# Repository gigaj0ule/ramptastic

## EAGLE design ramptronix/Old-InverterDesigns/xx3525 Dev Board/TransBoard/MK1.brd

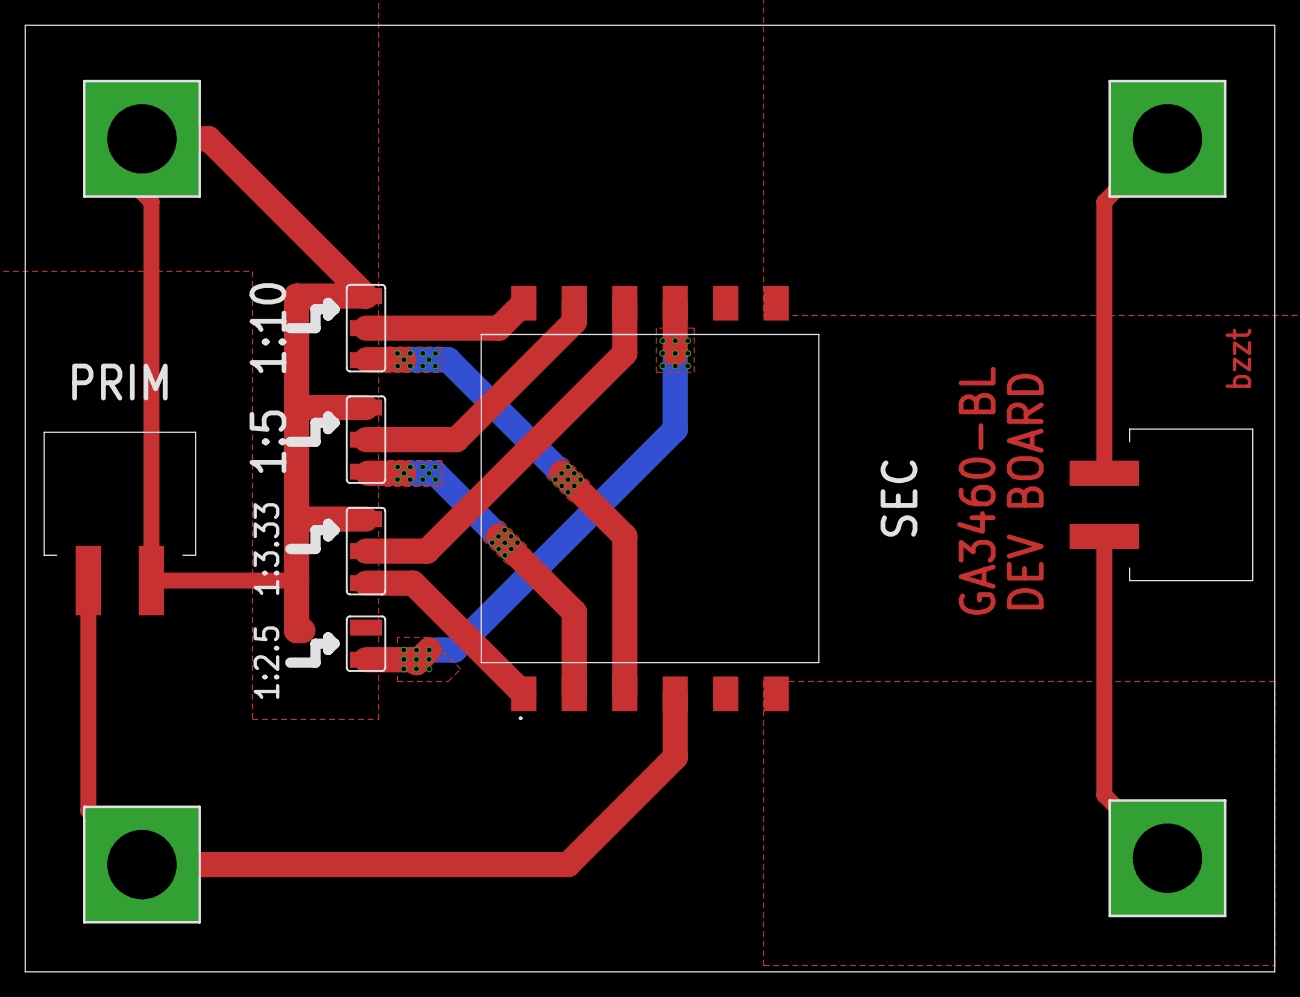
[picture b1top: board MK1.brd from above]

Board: 2 copper layers, 99.0 x 75.0 mm, 11 parts (0 on the bottom side), 11 nets.

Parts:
E$1: GA3460BL
E$2, E$3, E$5, E$7: 5,5-PAD-SQUARE
E$4, E$8, E$9: SJ_2W
E$6: SJW
E$10, E$11: 23059082

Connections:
1: E$1.1, E$4.3
2: E$1.2, E$9.3
3: E$1.3, E$8.3
9: E$1.9, E$6.1
10: E$1.10, E$4.2
11: E$1.11, E$9.2
12: E$1.12, E$8.2
GND: E$1.6, E$7.B5,5, E$10.2
OUT: E$2.B5,5, E$4.1, E$6.2, E$8.1, E$9.1, E$11.2
S$2: E$1.4, E$3.B5,5, E$11.1
SEC: E$1.7, E$5.B5,5, E$10.1

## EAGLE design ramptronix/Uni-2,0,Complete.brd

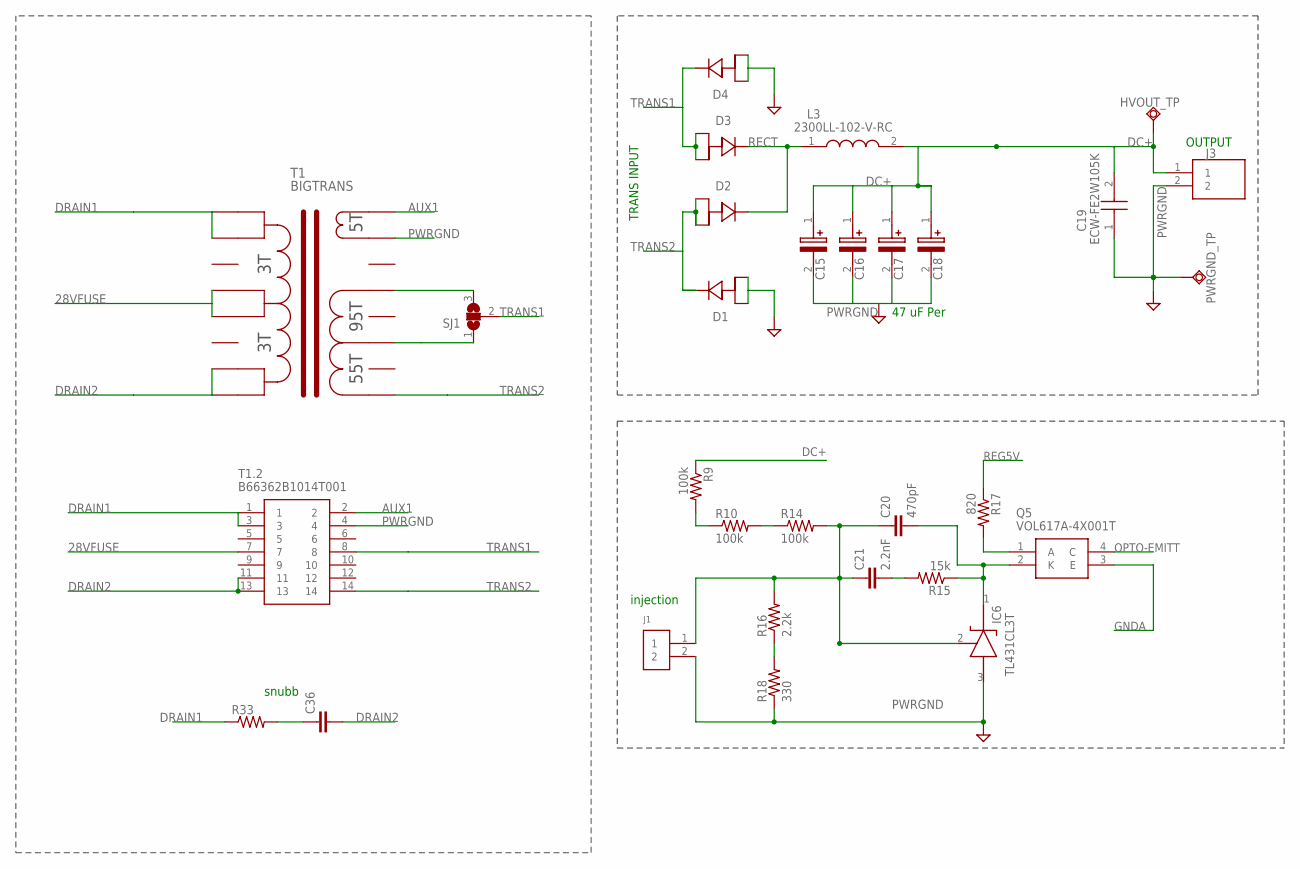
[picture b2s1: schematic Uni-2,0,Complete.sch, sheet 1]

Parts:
C15, C16, C17, C18: EEU-ED2V470S; CAPPRD750W85D1800H2200
C19: ECW-FE2W105K; ECWFE2W105K
C20: 470pF; C0603K
C21: 2.2nF; C0603K
C36: C-EUC1210K; C1210K
D1, D2, D3, D4: FERD20H60CG-TR; STB20N95K5
HVOUT_TP: TPSQPAD1-13; P1-13
IC6: TL431CL3T; SOT95P237X112-3N
J1: 61300211121
J3: 2305908-2; 23059082
L3: 2300LL-102-V-RC; 2300LL102VRC
PWRGND_TP: TPSQPAD1-13; P1-13
Q5: VOL617A-4X001T; SOP254P1015X230-4N
R9, R10, R14: 100k; R1206
R15: 15k; R0603
R16: 2.2k; R0805
R17: 820; R0603
R18: 330; R0805
R33: R-US_R1206; R1206
SJ1: SJ2WW; SJ_2W
T1: BIGTRANS; BIGTRANS!
T1.2: B66362B1014T001

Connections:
28VFUSE: T1.4, T1.5, T1.2.7; also elsewhere on the board
AUX1: T1.16, T1.2.2; also elsewhere on the board
DC+: C15.1 (+), C16.1 (+), C17.1 (+), C18.1 (+), C19.2, HVOUT_TP.TP, J3.1, L3.2, R9.1; also elsewhere on the board
DRAIN1: R33.1, T1.7, T1.8, T1.2.1, T1.2.3; also elsewhere on the board
DRAIN2: C36.2, T1.1, T1.2, T1.2.11, T1.2.13; also elsewhere on the board
GNDA: Q5.3 (E); also elsewhere on the board
unnamed: R9.2, R10.1
unnamed: C20.1, C21.1, IC6.2 (REF), J1.1, R14.2, R16.2
unnamed: SJ1.1, T1.11
unnamed: R10.2, R14.1
unnamed: R16.1, R18.2
unnamed: C20.2, IC6.1 (CATHODE), Q5.2 (K), R15.1
unnamed: Q5.1 (A), R17.2
unnamed: C21.2, R15.2
unnamed: SJ1.3, T1.13
unnamed: C36.1, R33.2
OPTO-EMITT: Q5.4 (C); also elsewhere on the board
PWRGND: C15.2 (-), C16.2 (-), C17.2 (-), C18.2 (-), C19.1, D1.1 (A1), D1.3 (A2), D4.1 (A1), D4.3 (A2), IC6.3 (ANODE), J1.2, J3.2, PWRGND_TP.TP, R18.1, T1.15, T1.2.4; also elsewhere on the board
RECT: D2.2 (K), D3.2 (K), L3.1
REG5V: R17.1; also elsewhere on the board
TRANS1: D3.1 (A1), D3.3 (A2), D4.2 (K), SJ1.2, T1.2.8
TRANS2: D1.2 (K), D2.1 (A1), D2.3 (A2), T1.9, T1.2.14

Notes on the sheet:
TRANS INPUT
OUTPUT
snubb
injection
47 uF Per

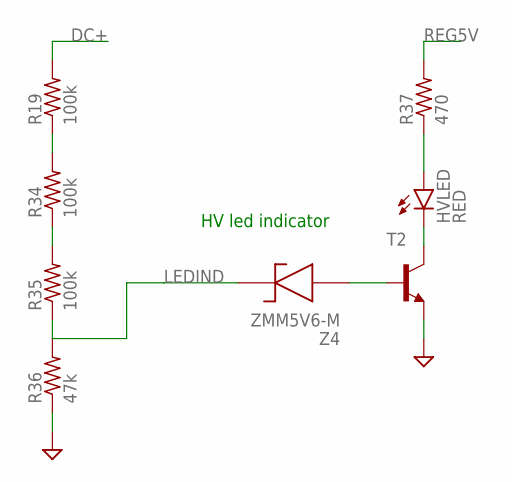
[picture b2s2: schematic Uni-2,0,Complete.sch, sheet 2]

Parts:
HVLED: RED; CHIPLED_0805
R19, R34, R35: 100k; R1206
R36: 47k; R0805
R37: 470; R0603
T2: MMBT3904LT1-NPN-SOT23-BEC; SOT23-BEC
Z4: ZMM5V6-M; BZV55C5V6L1

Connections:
DC+: R19.2; also elsewhere on the board
LEDIND: R35.1, R36.2, Z4.2 (K)
unnamed: R34.1, R35.2
unnamed: R19.1, R34.2
unnamed: T2.B, Z4.1 (A)
unnamed: HVLED.C, T2.C
unnamed: HVLED.A, R37.1
PWRGND: R36.1, T2.E; also elsewhere on the board
REG5V: R37.2; also elsewhere on the board

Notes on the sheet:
HV led indicator

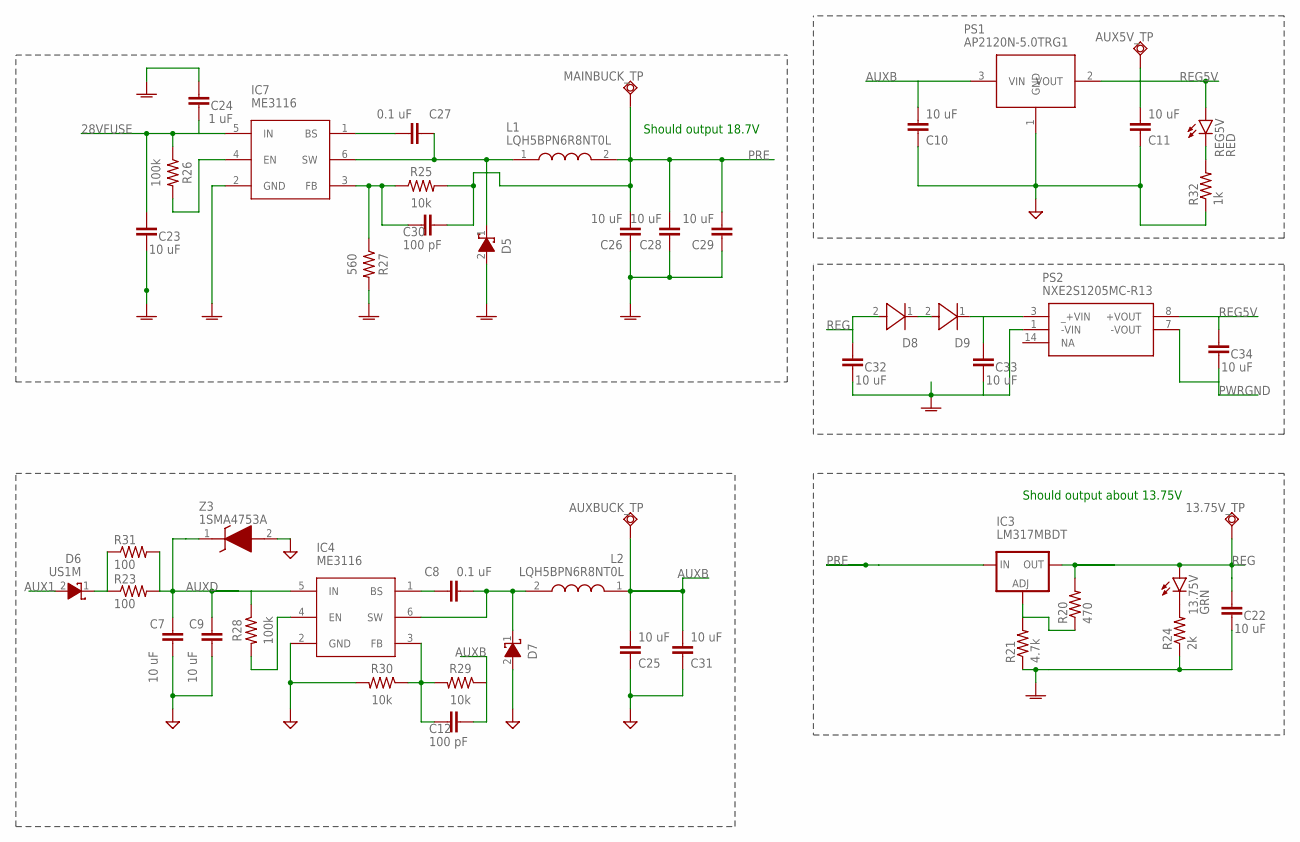
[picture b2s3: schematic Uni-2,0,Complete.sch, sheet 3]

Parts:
13.75V: GRN; CHIPLED_0805; LCSC_PART C72043
13.75V_TP: TPSQPAD1-17; P1-17
AUX5V_TP: TPSQPAD1-17; P1-17
AUXBUCK_TP: TPSQPAD1-17; P1-17
C7, C9: 10 uF; C0805K
C8, C27: 0.1 uF; C0603K; LCSC_PART C14663
C10, C25, C33, C34: 10 uF; C0603K; LCSC_PART C440198
C11: 10 uF; C0603K
C12, C30: 100 pF; C0402K; LCSC_PART C1546
C22, C23, C26, C28, C29, C32: 10 uF; C0805K; LCSC_PART C440198
C24: 1 uF; C0603K; LCSC_PART C440198
C31: 10 uF; C0402; LCSC_PART C440198
D5, D7: SCHOTTKY; DIOM5127X229N; LCSC_PART C22452
D6: US1M; DIOM5127X229N
D8, D9: SM4007PL; SOD3716X145N; LCSC_PART C64898
IC3: LM317MBDT; DPACK
IC4, IC7: ME3116; SOT95P280X100-6N; LCSC_PART C97643
L1, L2: LQH5BPN6R8NT0L; LQH5BPB100MT0L
MAINBUCK_TP: TPSQPAD1-17; P1-17
PS1: AP2120N-5.0TRG1; SOT95P240X120-3N
PS2: NXE2S1205MC-R13; NXE2S1205MCR13
R20: 470; R0603; LCSC_PART C22975
R21: 4.7k; R0603; LCSC_PART C22975
R23, R31: 100; R1206
R24: 2k; R0603; LCSC_PART C22975
R25, R29, R30: 10k; R0402; LCSC_PART C25779
R26, R28: 100k; R0402; LCSC_PART C25741
R27: 560; R0402; LCSC_PART C4177
R32: 1k; R0603; LCSC_PART C22975
REG5V: RED; CHIPLED_0805; LCSC_PART C72043
Z3: 1SMA4753A; DIOM5226X220N; LCSC_PART C362284

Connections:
28VFUSE: C23.2, C24.1, IC7.5 (IN), R26.1; also elsewhere on the board
AUX1: D6.2 (A); also elsewhere on the board
AUXB: AUXBUCK_TP.TP, C10.2, C12.1, C25.2, C31.2, L2.1, PS1.3 (VIN), R29.1
AUXD: C7.1, C9.1, IC4.5 (IN), R23.2, R28.1, R31.2, Z3.1 (K)
BS1: C27.2, IC7.1 (BS)
BS2: C8.1, IC4.1 (BS)
EN1: IC7.4 (EN), R26.2
EN2: IC4.4 (EN), R28.2
FB1: C30.2, IC7.3 (FB), R25.1, R27.1
FB2: C12.2, IC4.3 (FB), R29.2, R30.1
GNDA: C22.1, C23.1, C24.2, C26.1, C28.1, C29.1, C32.1, C33.1, D5.2 (A), IC7.2 (GND), PS2.1 (-VIN), R21.1, R24.1, R27.2; also elsewhere on the board
unnamed: D8.1 (K), D9.2 (A)
unnamed: IC3.1 (ADJ), R20.1, R21.2
unnamed: C33.2, D9.1 (K), PS2.3 (_+VIN)
unnamed: 13.75V.C, R24.2
unnamed: R32.2, REG5V.C
unnamed: D6.1 (K), R23.1, R31.1
PRE: C26.2, C28.2, C29.2, C30.1, IC3.3 (IN), L1.2, MAINBUCK_TP.TP, R25.2
PWRGND: C7.2, C9.2, C10.1, C11.1, C25.1, C31.1, C34.1, D7.2 (A), IC4.2 (GND), PS1.1 (GND), PS2.7 (-VOUT), R30.2, R32.1, Z3.2 (A); also elsewhere on the board
REG: 13.75V.A, 13.75V_TP.TP, C22.2, C32.2, D8.2 (A), IC3.4 (OUT), R20.2; also elsewhere on the board
REG5V: AUX5V_TP.TP, C11.2, C34.2, PS1.2 (VOUT), PS2.8 (+VOUT), REG5V.A; also elsewhere on the board
SWITCH1: C27.1, D5.1 (K), IC7.6 (SW), L1.1
SWITCH2: C8.2, D7.1 (K), IC4.6 (SW), L2.2

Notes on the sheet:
Should output 18.7V
Should output about 13.75V

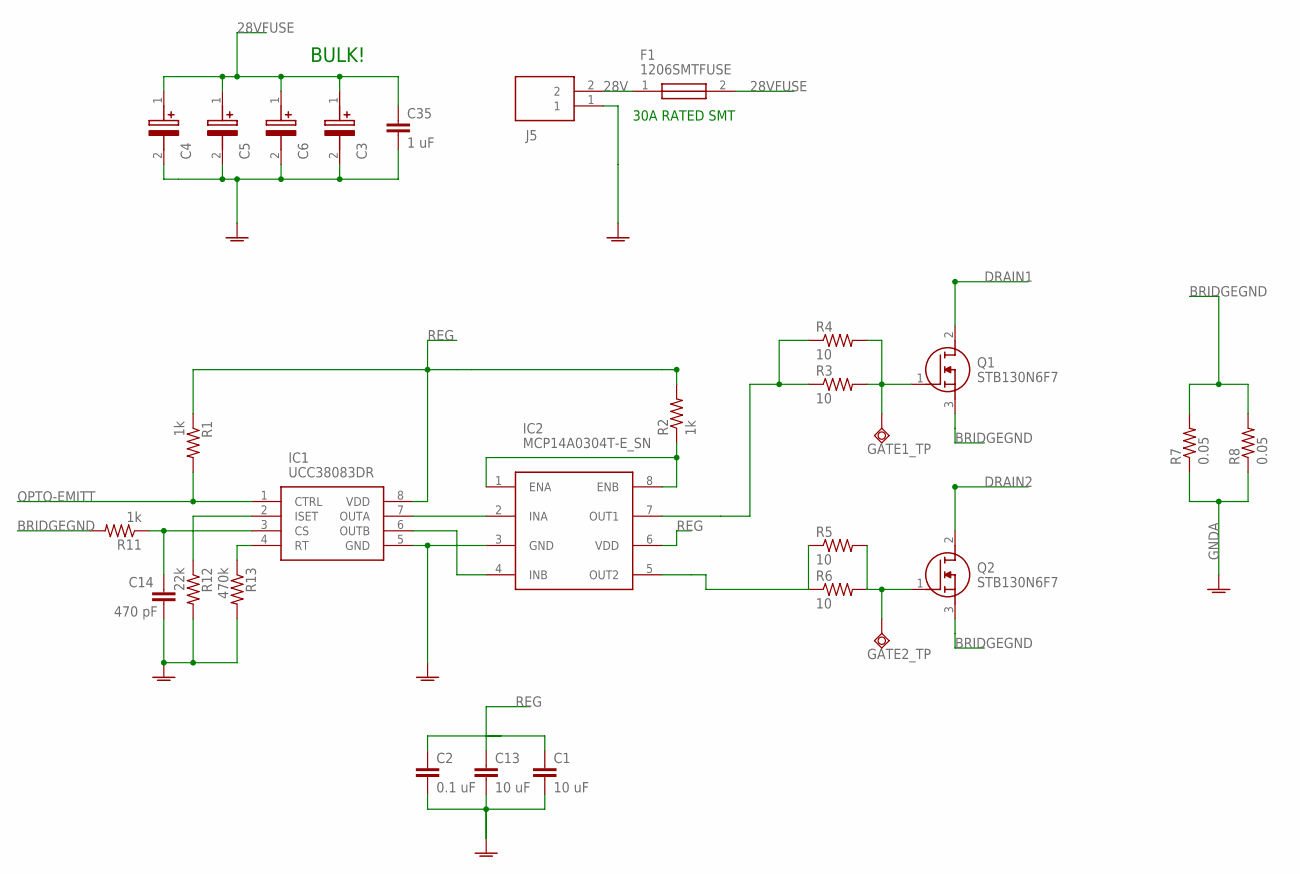
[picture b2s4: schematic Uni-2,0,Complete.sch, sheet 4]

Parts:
C1, C13: 10 uF; C0603K; LCSC_PART C440198
C2: 0.1 uF; C0603K; LCSC_PART C440198
C3, C4, C5, C6: OVK151M1VTR-10131; 16SVF1000M
C14: 470 pF; C0603K; LCSC_PART C1620
C35: 1 uF; C0805K; LCSC_PART C440198
F1: 1206SMTFUSE
GATE1_TP, GATE2_TP: TPSQPAD1-17; P1-17
IC1: UCC38083DR; SOIC127P600X175-8N
IC2: MCP14A0304T-E_SN; SOIC127P600X175-8N
J5: 2305908-2; 23059082
Q1, Q2: STB130N6F7; D2PAK
R1: 1k; R0603; LCSC_PART C22975
R2: 1k; R0402
R3, R4, R5, R6: 10; R0805
R7, R8: 0.05; R2512
R11: 1k; R0603; LCSC_PART C21190
R12: 22k; R0603; LCSC_PART C31850
R13: 470k; R0603; LCSC_PART C25811

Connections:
28V: F1.1, J5.2
28VFUSE: C3.1 (+), C4.1 (+), C5.1 (+), C6.1 (+), C35.1, F1.2; also elsewhere on the board
BRIDGEGND: Q1.3 (S), Q2.3 (S), R7.2, R8.2, R11.2
CS-IN: C14.1, IC1.3 (CS), R11.1
DRAIN1: Q1.2 (D); also elsewhere on the board
DRAIN2: Q2.2 (D); also elsewhere on the board
GNDA: C1.2, C2.2, C3.2 (-), C4.2 (-), C5.2 (-), C6.2 (-), C13.2, C14.2, C35.2, IC1.5 (GND), IC2.3 (GND), J5.1, R7.1, R8.1, R12.2, R13.2; also elsewhere on the board
unnamed: IC1.7 (OUTA), IC2.2 (INA)
unnamed: IC1.6 (OUTB), IC2.4 (INB)
unnamed: IC2.1 (ENA), IC2.8 (ENB), R2.1
unnamed: IC2.7 (OUT1), R3.1, R4.1
unnamed: IC2.5 (OUT2), R5.1, R6.1
unnamed: IC1.2 (ISET), R12.1
OPTO-EMITT: IC1.1 (CTRL), R1.2; also elsewhere on the board
Q1G: GATE1_TP.TP, Q1.1 (G), R3.2, R4.2
Q2G: GATE2_TP.TP, Q2.1 (G), R5.2, R6.2
REG: C1.1, C2.1, C13.1, IC1.8 (VDD), IC2.6 (VDD), R1.1, R2.2; also elsewhere on the board
RT: IC1.4 (RT), R13.1

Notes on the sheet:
BULK!
30A RATED SMT

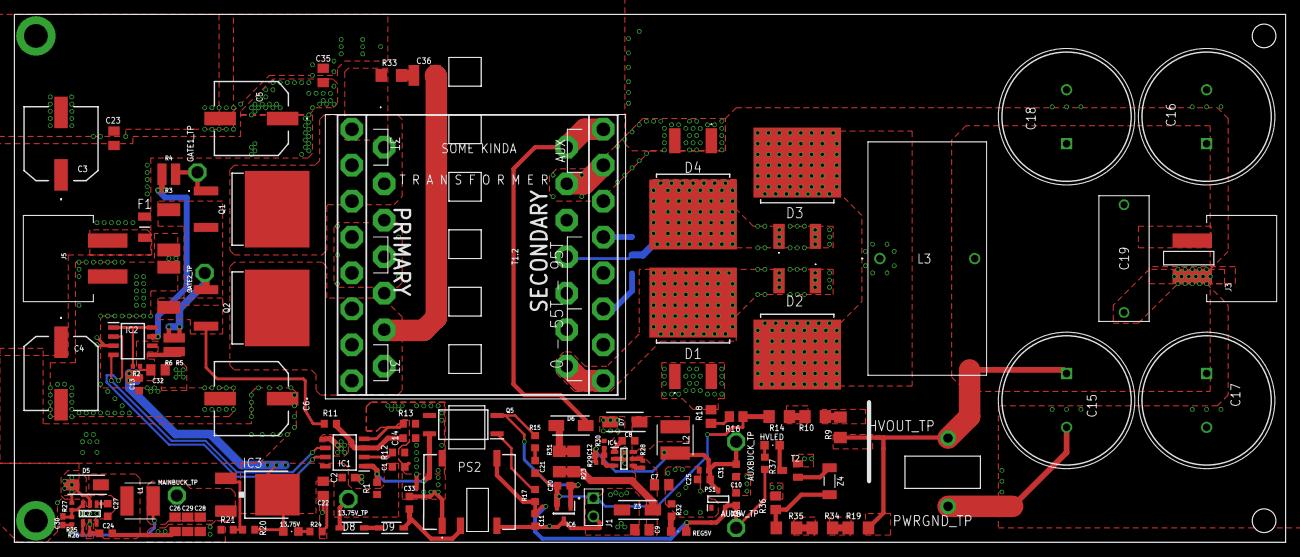
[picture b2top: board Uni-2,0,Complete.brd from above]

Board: 2 copper layers, 177.0 x 73.5 mm, 116 parts (1 on the bottom side), 58 nets.

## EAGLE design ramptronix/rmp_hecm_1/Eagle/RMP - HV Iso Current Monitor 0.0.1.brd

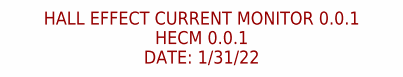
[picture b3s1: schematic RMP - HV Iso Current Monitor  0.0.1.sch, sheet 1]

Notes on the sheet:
HALL EFFECT CURRENT MONITOR 0.0.1 HECM 0.0.1 DATE: 1/31/22

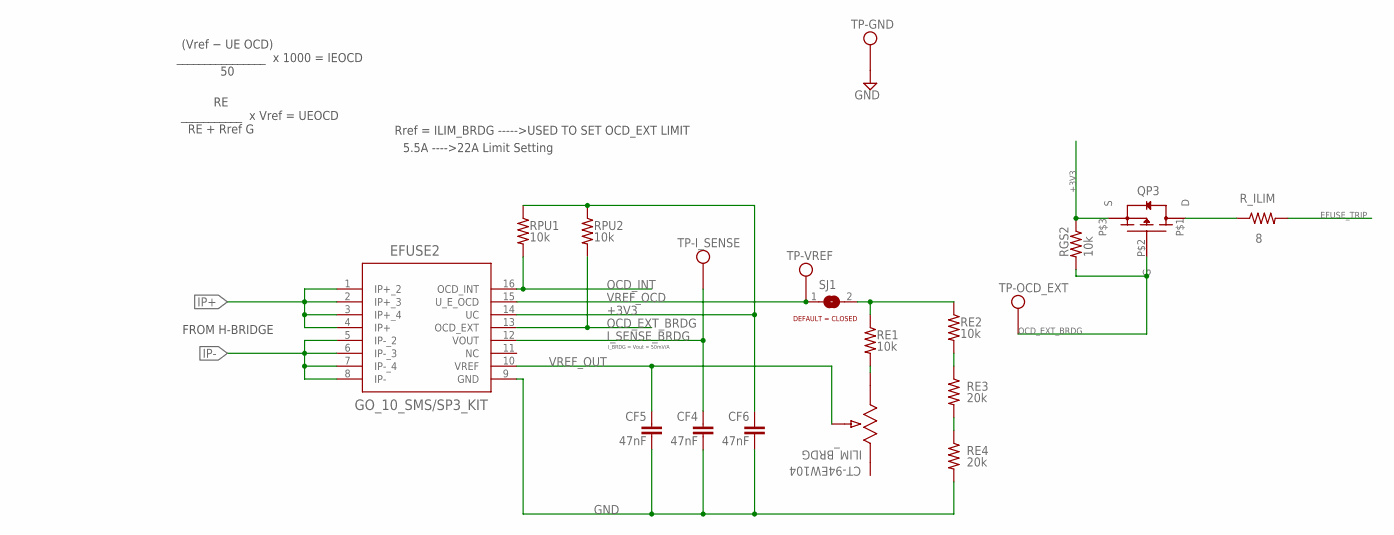
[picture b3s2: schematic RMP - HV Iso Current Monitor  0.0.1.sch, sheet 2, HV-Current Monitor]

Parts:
CF4, CF5, CF6: 47nF; C0603; LCSC_PART C76712
EFUSE2: GO_10_SMS/SP3_KIT; SOIC_GO_10_SM_LEM; LCSC_PART DNP
ILIM_BRDG: CT-94EW104; POT_CT-94EW_NDC; LCSC_PART DNP
QP3: PFET-(SOT-23-3)(TO-236-3)(SC-59); SOT23,SC-59,TO-236-3; LCSC_PART C489594
RE1, RE2: 10k; R0603; LCSC_PART C116677
RE3, RE4: 20k; R0603; LCSC_PART C118368
RGS2: 10k; R0603; LCSC_PART C116677
RPU1, RPU2: 10k; R0603; LCSC_PART C116677
R_ILIM: 8; R1206; LCSC_PART C114478
SJ1: SJ
TP-GND: THM_TESTPOINT_5000_SERIES; THM-TESTPOINT; LCSC_PART DNP
TP-I_SENSE: THM_TESTPOINT_5000_SERIES; THM-TESTPOINT; LCSC_PART DNP
TP-OCD_EXT: THM_TESTPOINT_5000_SERIES; THM-TESTPOINT; LCSC_PART DNP
TP-VREF: THM_TESTPOINT_5000_SERIES; THM-TESTPOINT; LCSC_PART DNP

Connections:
+3V3: CF6.1, EFUSE2.14 (UC), QP3.P$3 (S), RGS2.1, RPU1.1, RPU2.1; also elsewhere on the board
EFUSE_TRIP: R_ILIM.2; also elsewhere on the board
GND: CF4.2, CF5.2, CF6.2, EFUSE2.9 (GND), RE4.2, TP-GND.P1; also elsewhere on the board
IP+: EFUSE2.1 (IP+_2), EFUSE2.2 (IP+_3), EFUSE2.3 (IP+_4), EFUSE2.4 (IP+); also elsewhere on the board
IP-: EFUSE2.5 (IP-_2), EFUSE2.6 (IP-_3), EFUSE2.7 (IP-_4), EFUSE2.8 (IP-); also elsewhere on the board
I_SENSE_BRDG: CF4.1, EFUSE2.12 (VOUT), TP-I_SENSE.P1; also elsewhere on the board
unnamed: RE1.1, RE2.1, SJ1.2
unnamed: RE2.2, RE3.1
unnamed: RE3.2, RE4.1
unnamed: QP3.P$1 (D), R_ILIM.1
unnamed: ILIM_BRDG.3, RE1.2
OCD_EXT_BRDG: EFUSE2.13 (OCD_EXT), QP3.P$2 (G), RGS2.2, RPU2.2, TP-OCD_EXT.P1
OCD_INT: EFUSE2.16 (OCD_INT), RPU1.2
VREF_OCD: EFUSE2.15 (U_E_OCD), SJ1.1, TP-VREF.P1; also elsewhere on the board
VREF_OUT: CF5.1, EFUSE2.10 (VREF), ILIM_BRDG.2

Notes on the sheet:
FROM H-BRIDGE
Rref = ILIM_BRDG ----->USED TO SET OCD_EXT LIMIT
(Vref − UE OCD) ________________ x 1000 = IEOCD 50
RE ___________ x Vref = UEOCD RE + Rref G
I_BRDG = Vout = 50mV/A
5.5A ---->22A Limit Setting
DEFAULT = CLOSED

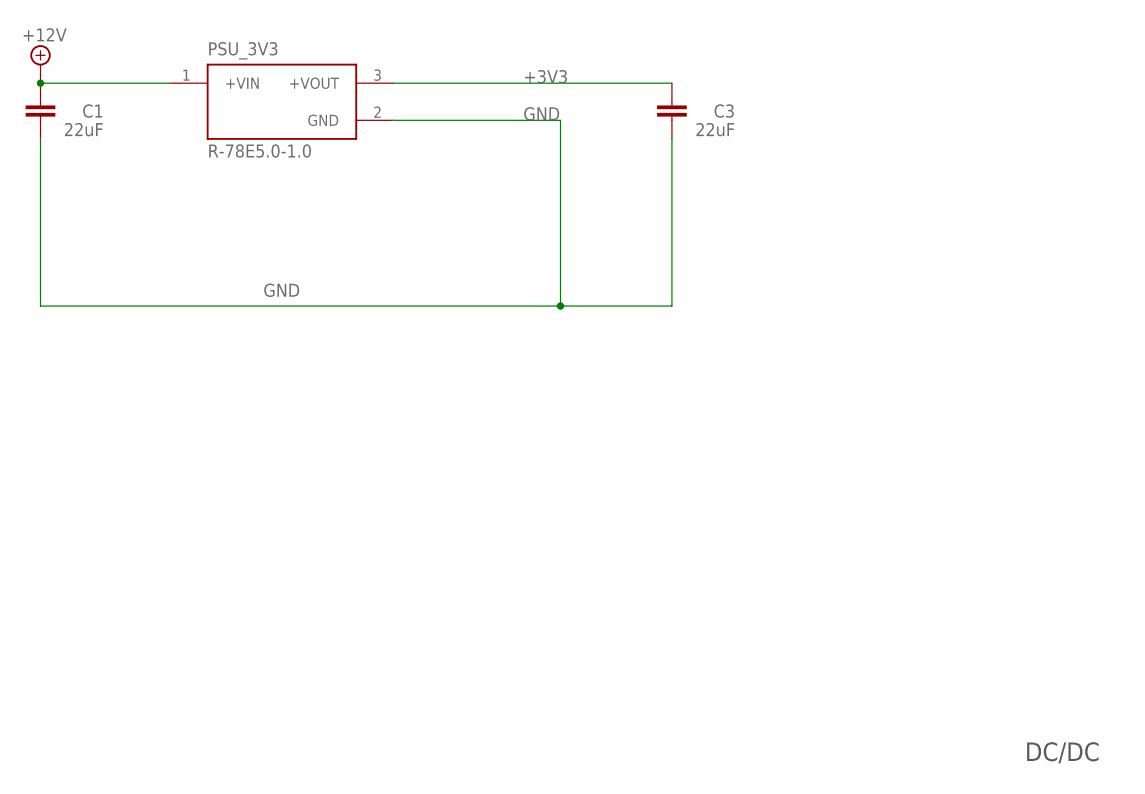
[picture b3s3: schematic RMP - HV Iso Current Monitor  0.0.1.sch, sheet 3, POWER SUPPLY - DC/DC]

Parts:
C1, C3: 22uF; C1206; LCSC_PART C77091
PSU_3V3: R-78E5.0-1.0; CONV_R-78E5.0-1.0; LCSC_PART DNP

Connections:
+3V3: C3.2, PSU_3V3.3 (+VOUT); also elsewhere on the board
+12V: C1.2, PSU_3V3.1 (+VIN); also elsewhere on the board
GND: C1.1, C3.1, PSU_3V3.2 (GND); also elsewhere on the board

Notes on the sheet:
DC/DC

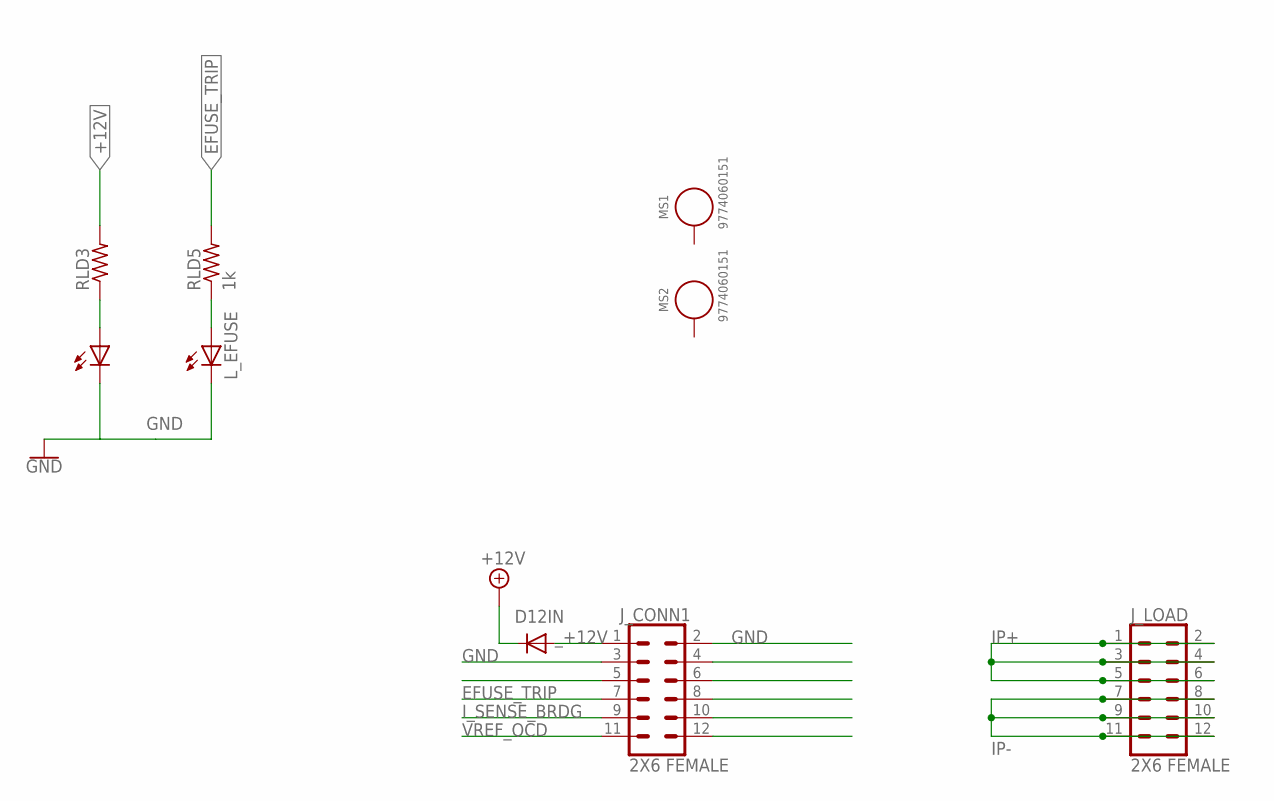
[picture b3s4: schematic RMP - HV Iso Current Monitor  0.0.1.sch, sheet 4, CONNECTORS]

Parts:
D12IN: DIODESMA; SMADIODE; LCSC_PART C110531
J_CONN1: 2X6 FEMALE; 2X6; LCSC_PART DNP
J_LOAD: 2X6 FEMALE; 2X6; LCSC_PART DNP
L_12V: LEDCHIPLED_1206; CHIPLED_1206; LCSC_PART C434439
L_EFUSE: LEDCHIPLED_1206; CHIPLED_1206; LCSC_PART C434439
MS1, MS2: 9774060151; WA-SMSI_9774060151
RLD3, RLD5: 1k; R1206; LCSC_PART C115421

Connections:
+12V: D12IN.C, RLD3.2; also elsewhere on the board
EFUSE_TRIP: J_CONN1.7, RLD5.2; also elsewhere on the board
GND: J_CONN1.2, J_CONN1.3, L_12V.C; also elsewhere on the board
GND2: L_EFUSE.C
IP+: J_LOAD.1, J_LOAD.2, J_LOAD.3, J_LOAD.4, J_LOAD.5, J_LOAD.6; also elsewhere on the board
IP-: J_LOAD.7, J_LOAD.8, J_LOAD.9, J_LOAD.10, J_LOAD.11, J_LOAD.12; also elsewhere on the board
I_SENSE_BRDG: J_CONN1.9; also elsewhere on the board
unnamed: L_12V.A, RLD3.1
unnamed: L_EFUSE.A, RLD5.1
VREF_OCD: J_CONN1.11; also elsewhere on the board
_+12V: D12IN.A, J_CONN1.1

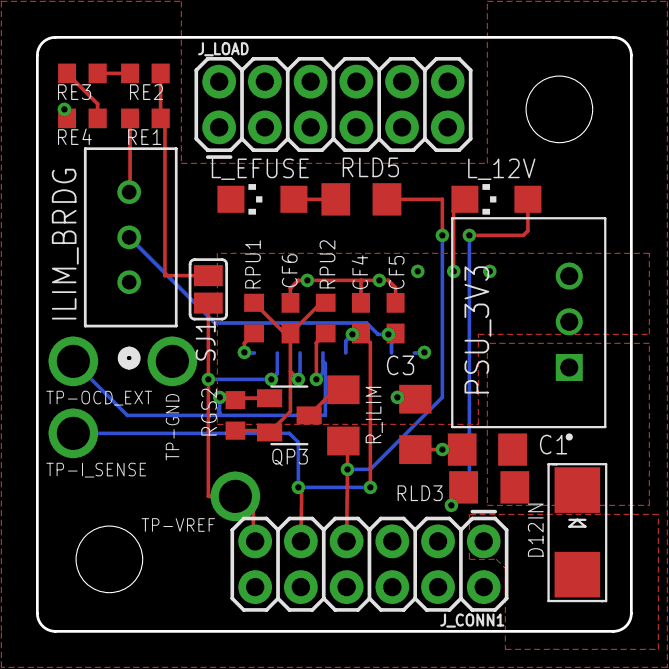
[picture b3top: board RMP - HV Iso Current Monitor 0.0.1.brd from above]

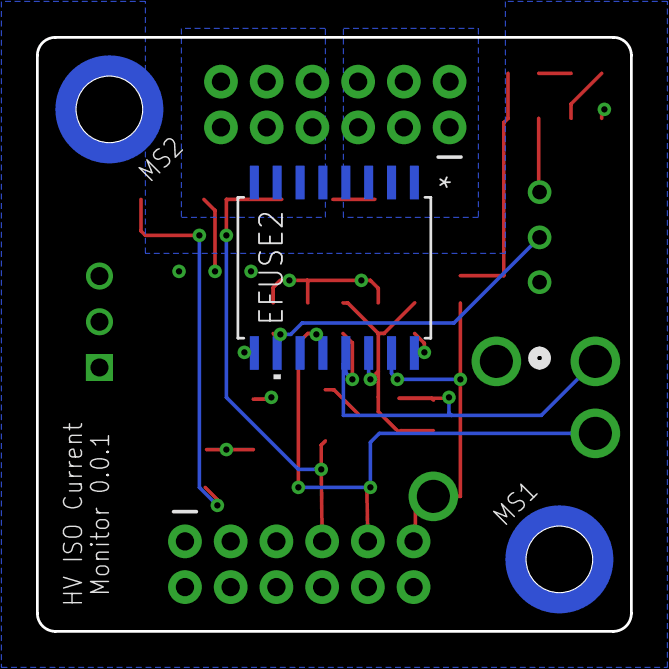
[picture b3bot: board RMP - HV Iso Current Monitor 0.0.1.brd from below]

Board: 4 copper layers, 33.0 x 33.0 mm, 31 parts (3 on the bottom side), 19 nets.

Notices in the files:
parts and their libraries:
KVRLABS-Amplifiers: COPYRIGHT: Copyright (C) 2021 Ultra Librarian. All rights reserved.
SparkFun-PowerSymbols: Licensing: Creative Commons ShareAlike 4.0 International - https://creativecommons.org/licenses/by-sa/4.0
Eagle_WA-SMSI: Copyright: Würth Elektronik
